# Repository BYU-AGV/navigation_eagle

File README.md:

# navigation_eagle
eagle projects for the navigation team.

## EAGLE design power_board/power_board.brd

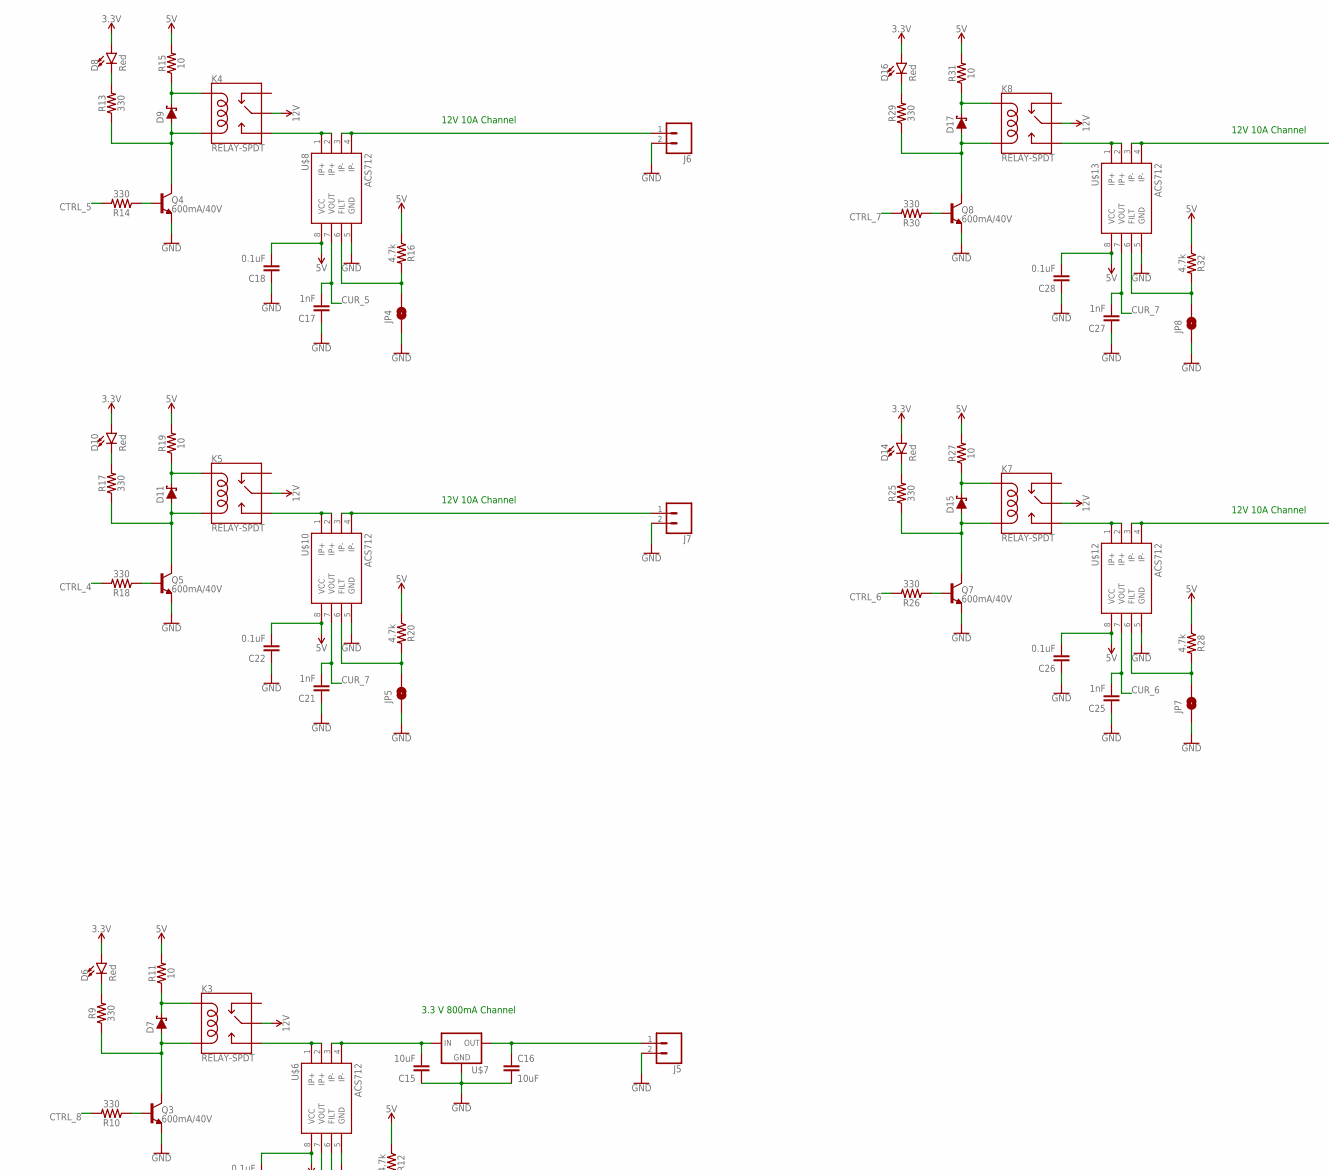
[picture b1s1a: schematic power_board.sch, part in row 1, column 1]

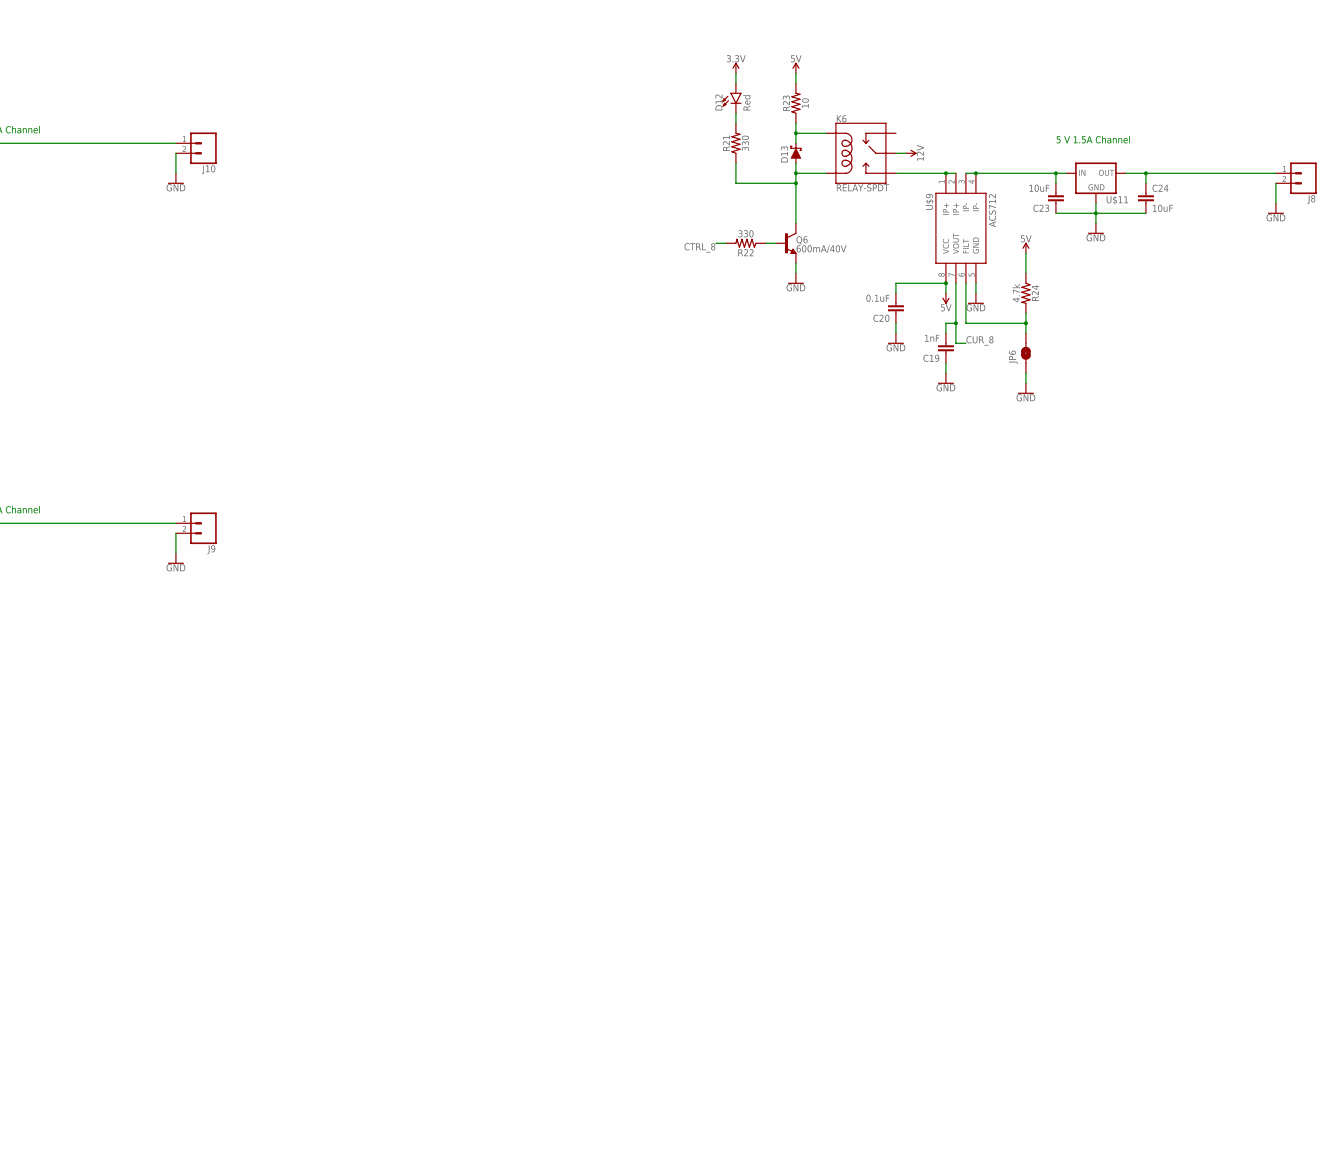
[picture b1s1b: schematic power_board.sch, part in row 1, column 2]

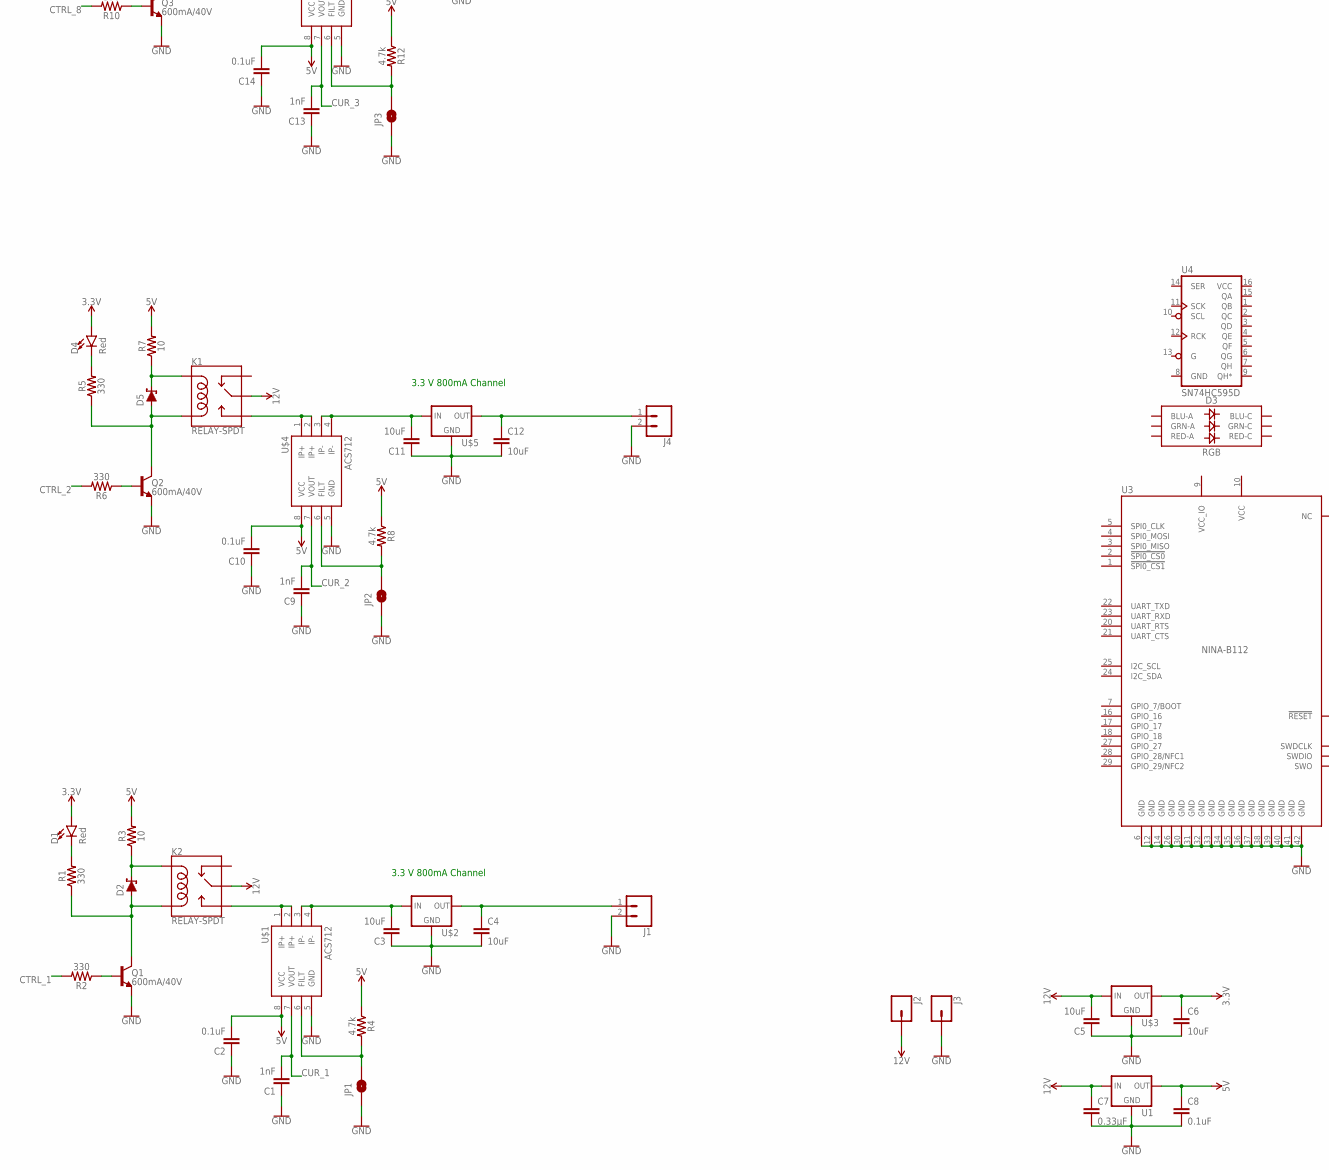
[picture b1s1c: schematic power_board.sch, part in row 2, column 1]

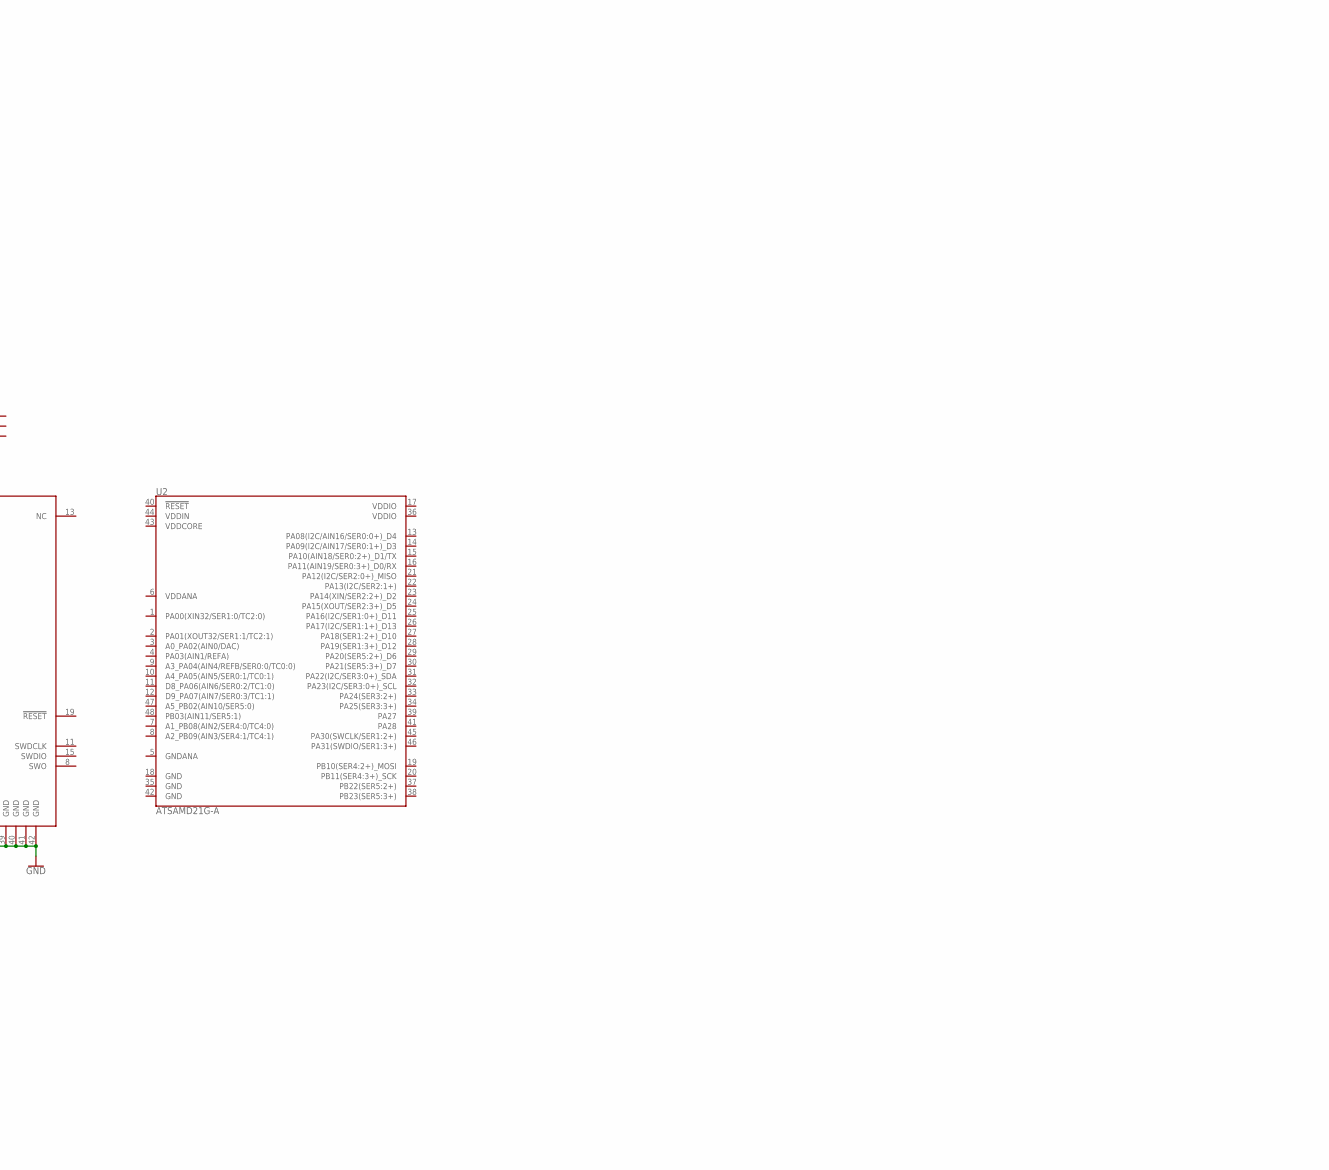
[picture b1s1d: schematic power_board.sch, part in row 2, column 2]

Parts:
C1, C9, C13, C17, C19, C21, C25, C27: 1nF; 0603
C2, C8, C10, C14, C18, C20, C22, C26, C28: 0.1uF; 0603
C3, C4, C5, C6, C11, C12, C15, C16, C23, C24: 10uF; 0603
C7: 0.33µF; 0805
D1, D4, D6, D8, D10, D12, D14, D16: Red; LED-0603
D2, D5, D7, D9, D11, D13, D15, D17: 1A/23V/620mV; SOD-323
D3: RGB; PLCC-6-LED
J1, J4, J5, J6, J7, J8, J9, J10: CONN_023.5MM; SCREWTERMINAL-3.5MM-2
J2, J3: CONN_01PTH_2MM; 1X01_2MM
JP1, JP2, JP3, JP4, JP5, JP6, JP7, JP8: JUMPER-SMT_2_NO_NO-SILK_ROUND; SMT-JUMPER_2_NO_NO-SILK_ROUND
K1, K2, K3, K4, K5, K6, K7, K8: RELAY-SPDT; RELAY_G5LE
Q1, Q2, Q3, Q4, Q5, Q6, Q7, Q8: 600mA/40V; SOT23-3
R1, R2, R5, R6, R9, R10, R13, R14, R17, R18, R21, R22, R25, R26, R29, R30: 330; 0603
R3, R7, R11, R15, R19, R23, R27, R31: 10; 0603
R4, R8, R12, R16, R20, R24, R28, R32: 4.7k; 0603
U1: V_REG_78XX-TO-220; TO-220-ALT
U2: ATSAMD21G-A; TQFP-48
U3: NINA-B112; NINA112-42
U4: SN74HC595D; SO16
U$1, U$4, U$6, U$8, U$9, U$10, U$12, U$13: ACS712; SO08
U$2, U$3, U$5, U$7: 3.3V Voltage Regulator; SOT223
U$11: 3.3V Voltage Regulator; TO-220-ALT

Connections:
3.3V: C6.1, D1.A, D4.A, D6.A, D8.A, D10.A, D12.A, D14.A, D16.A, U$3.2 (OUT)
5V: C2.2, C8.1, C10.2, C14.2, C18.2, C20.2, C22.2, C26.2, C28.2, R3.2, R4.1, R7.2, R8.1, R11.2, R12.1, R15.2, R16.1, R19.2, R20.1, R23.2, R24.1, R27.2, R28.1, R31.2, R32.1, U1.OUT, U$1.8 (VCC), U$4.8 (VCC), U$6.8 (VCC), U$8.8 (VCC), U$9.8 (VCC), U$10.8 (VCC), U$12.8 (VCC), U$13.8 (VCC)
12V: C5.2, C7.1, J2.1, K1.1 (MAIN), K2.1 (MAIN), K3.1 (MAIN), K4.1 (MAIN), K5.1 (MAIN), K6.1 (MAIN), K7.1 (MAIN), K8.1 (MAIN), U1.IN, U$3.3 (IN)
CTRL_1: R2.2
CTRL_2: R6.2
CTRL_4: R18.2
CTRL_5: R14.2
CTRL_6: R26.2
CTRL_7: R30.2
CTRL_8: R10.2, R22.2
CUR_1: C1.2, U$1.7 (VOUT)
CUR_2: C9.2, U$4.7 (VOUT)
CUR_3: C13.2, U$6.7 (VOUT)
CUR_5: C17.2, U$8.7 (VOUT)
CUR_6: C25.2, U$12.7 (VOUT)
CUR_7: C21.2, C27.2, U$10.7 (VOUT), U$13.7 (VOUT)
CUR_8: C19.2, U$9.7 (VOUT)
GND: C1.1, C2.1, C3.1, C4.2, C5.1, C6.2, C7.2, C8.2, C9.1, C10.1, C11.1, C12.2, C13.1, C14.1, C15.1, C16.2, C17.1, C18.1, C19.1, C20.1, C21.1, C22.1, C23.1, C24.2, C25.1, C26.1, C27.1, C28.1, J1.2, J3.1, J4.2, J5.2, J6.2, J7.2, J8.2, J9.2, J10.2, JP1.1, JP2.1, JP3.1, JP4.1, JP5.1, JP6.1, JP7.1, JP8.1, Q1.2 (E), Q2.2 (E), Q3.2 (E), Q4.2 (E), Q5.2 (E), Q6.2 (E), Q7.2 (E), Q8.2 (E), U1.GND, U3.6 (GND), U3.12 (GND), U3.14 (GND), U3.26 (GND), U3.30 (GND), U3.31 (GND), U3.32 (GND), U3.33 (GND), U3.34 (GND), U3.35 (GND), U3.36 (GND), U3.37 (GND), U3.38 (GND), U3.39 (GND), U3.40 (GND), U3.41 (GND), U3.42 (GND), U4.8 (GND), U$1.5 (GND), U$2.1 (GND), U$3.1 (GND), U$4.5 (GND), U$5.1 (GND), U$6.5 (GND), U$7.1 (GND), U$8.5 (GND), U$9.5 (GND), U$10.5 (GND), U$11.GND, U$12.5 (GND), U$13.5 (GND)
unnamed: K2.3 (NO), U$1.1 (IP+), U$1.2 (IP+)
unnamed: C3.2, U$1.3 (IP-), U$1.4 (IP-), U$2.3 (IN)
unnamed: C4.1, J1.1, U$2.2 (OUT)
unnamed: D2.A, K2.5 (COIL2), Q1.3 (C), R1.1
unnamed: D2.C, K2.2 (COIL1), R3.1
unnamed: D1.C, R1.2
unnamed: JP1.2, R4.2, U$1.6 (FILT)
unnamed: D5.A, K1.5 (COIL2), Q2.3 (C), R5.1
unnamed: Q1.1 (B), R2.1
unnamed: D5.C, K1.2 (COIL1), R7.1
unnamed: D4.C, R5.2
unnamed: Q2.1 (B), R6.1
unnamed: C11.2, U$4.3 (IP-), U$4.4 (IP-), U$5.3 (IN)
unnamed: K1.3 (NO), U$4.1 (IP+), U$4.2 (IP+)
unnamed: JP2.2, R8.2, U$4.6 (FILT)
unnamed: C12.1, J4.1, U$5.2 (OUT)
unnamed: D7.A, K3.5 (COIL2), Q3.3 (C), R9.1
unnamed: D7.C, K3.2 (COIL1), R11.1
unnamed: D6.C, R9.2
unnamed: Q3.1 (B), R10.1
unnamed: C15.2, U$6.3 (IP-), U$6.4 (IP-), U$7.3 (IN)
unnamed: K3.3 (NO), U$6.1 (IP+), U$6.2 (IP+)
unnamed: JP3.2, R12.2, U$6.6 (FILT)
unnamed: C16.1, J5.1, U$7.2 (OUT)
unnamed: D9.A, K4.5 (COIL2), Q4.3 (C), R13.1
unnamed: J7.1, U$10.3 (IP-), U$10.4 (IP-)
unnamed: D9.C, K4.2 (COIL1), R15.1
unnamed: D8.C, R13.2
unnamed: Q4.1 (B), R14.1
unnamed: K4.3 (NO), U$8.1 (IP+), U$8.2 (IP+)
unnamed: JP4.2, R16.2, U$8.6 (FILT)
unnamed: J6.1, U$8.3 (IP-), U$8.4 (IP-)
unnamed: D11.A, K5.5 (COIL2), Q5.3 (C), R17.1
unnamed: D11.C, K5.2 (COIL1), R19.1
unnamed: D10.C, R17.2
unnamed: Q5.1 (B), R18.1
unnamed: D13.A, K6.5 (COIL2), Q6.3 (C), R21.1
unnamed: K5.3 (NO), U$10.1 (IP+), U$10.2 (IP+)
unnamed: JP5.2, R20.2, U$10.6 (FILT)
unnamed: D13.C, K6.2 (COIL1), R23.1
unnamed: D12.C, R21.2
unnamed: Q6.1 (B), R22.1
unnamed: C23.2, U$9.3 (IP-), U$9.4 (IP-), U$11.IN
unnamed: K6.3 (NO), U$9.1 (IP+), U$9.2 (IP+)
unnamed: JP6.2, R24.2, U$9.6 (FILT)
unnamed: C24.1, J8.1, U$11.OUT
unnamed: D15.A, K7.5 (COIL2), Q7.3 (C), R25.1
unnamed: D15.C, K7.2 (COIL1), R27.1
unnamed: D14.C, R25.2
unnamed: Q7.1 (B), R26.1
unnamed: K7.3 (NO), U$12.1 (IP+), U$12.2 (IP+)
unnamed: JP7.2, R28.2, U$12.6 (FILT)
unnamed: J9.1, U$12.3 (IP-), U$12.4 (IP-)
unnamed: D17.A, K8.5 (COIL2), Q8.3 (C), R29.1
unnamed: D17.C, K8.2 (COIL1), R31.1
unnamed: D16.C, R29.2
unnamed: Q8.1 (B), R30.1
unnamed: K8.3 (NO), U$13.1 (IP+), U$13.2 (IP+)
unnamed: JP8.2, R32.2, U$13.6 (FILT)
unnamed: J10.1, U$13.3 (IP-), U$13.4 (IP-)
VCC: U3.10 (VCC), U4.16 (VCC)
VCC_IO: U3.9 (VCC_IO)

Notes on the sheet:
3.3 V 800mA Channel
12V 10A Channel
5 V 1.5A Channel

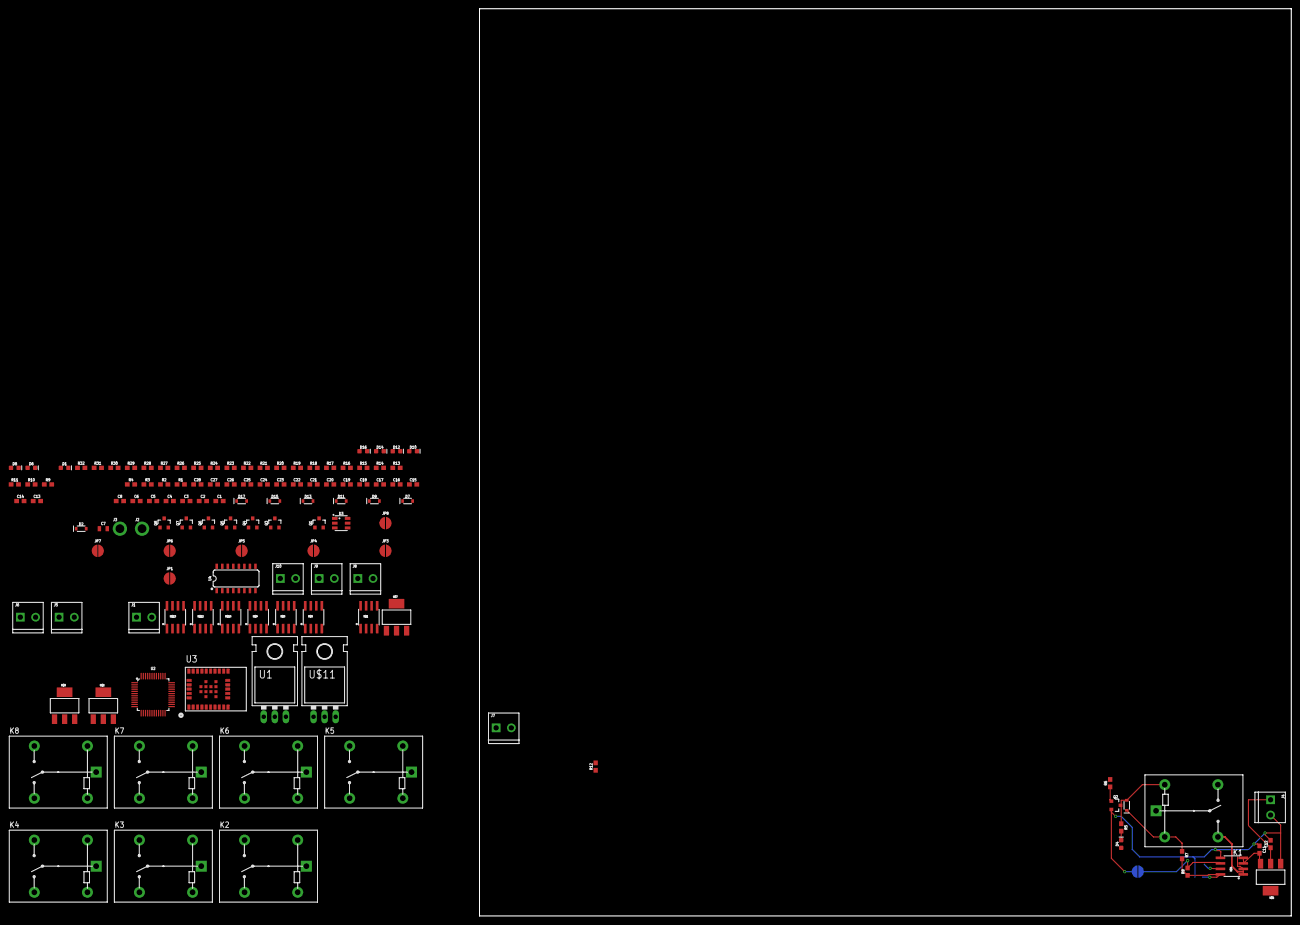
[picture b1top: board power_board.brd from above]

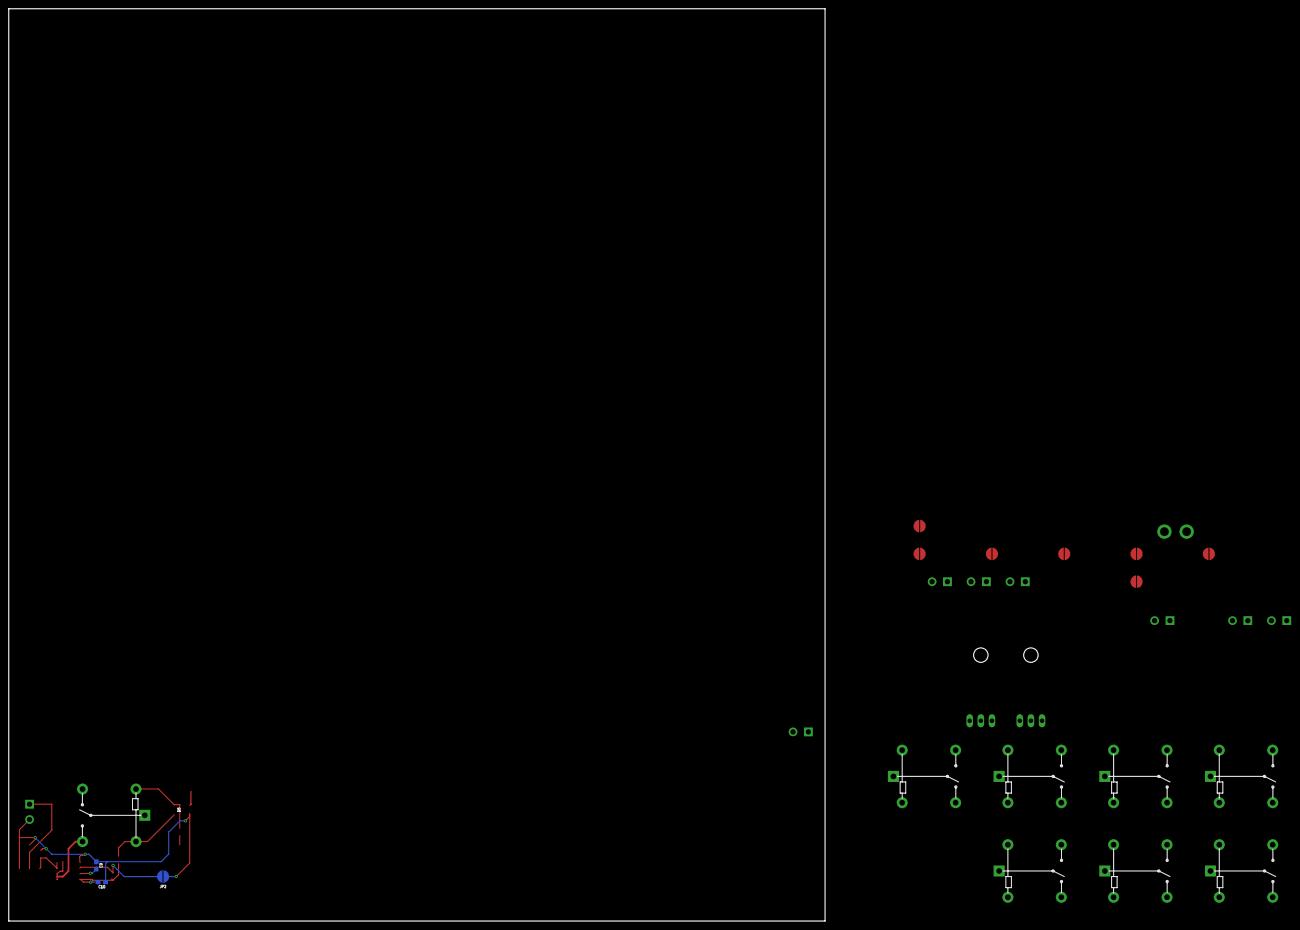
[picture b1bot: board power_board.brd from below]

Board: 2 copper layers, 186.4 x 208.3 mm, 128 parts (3 on the bottom side), 73 nets.

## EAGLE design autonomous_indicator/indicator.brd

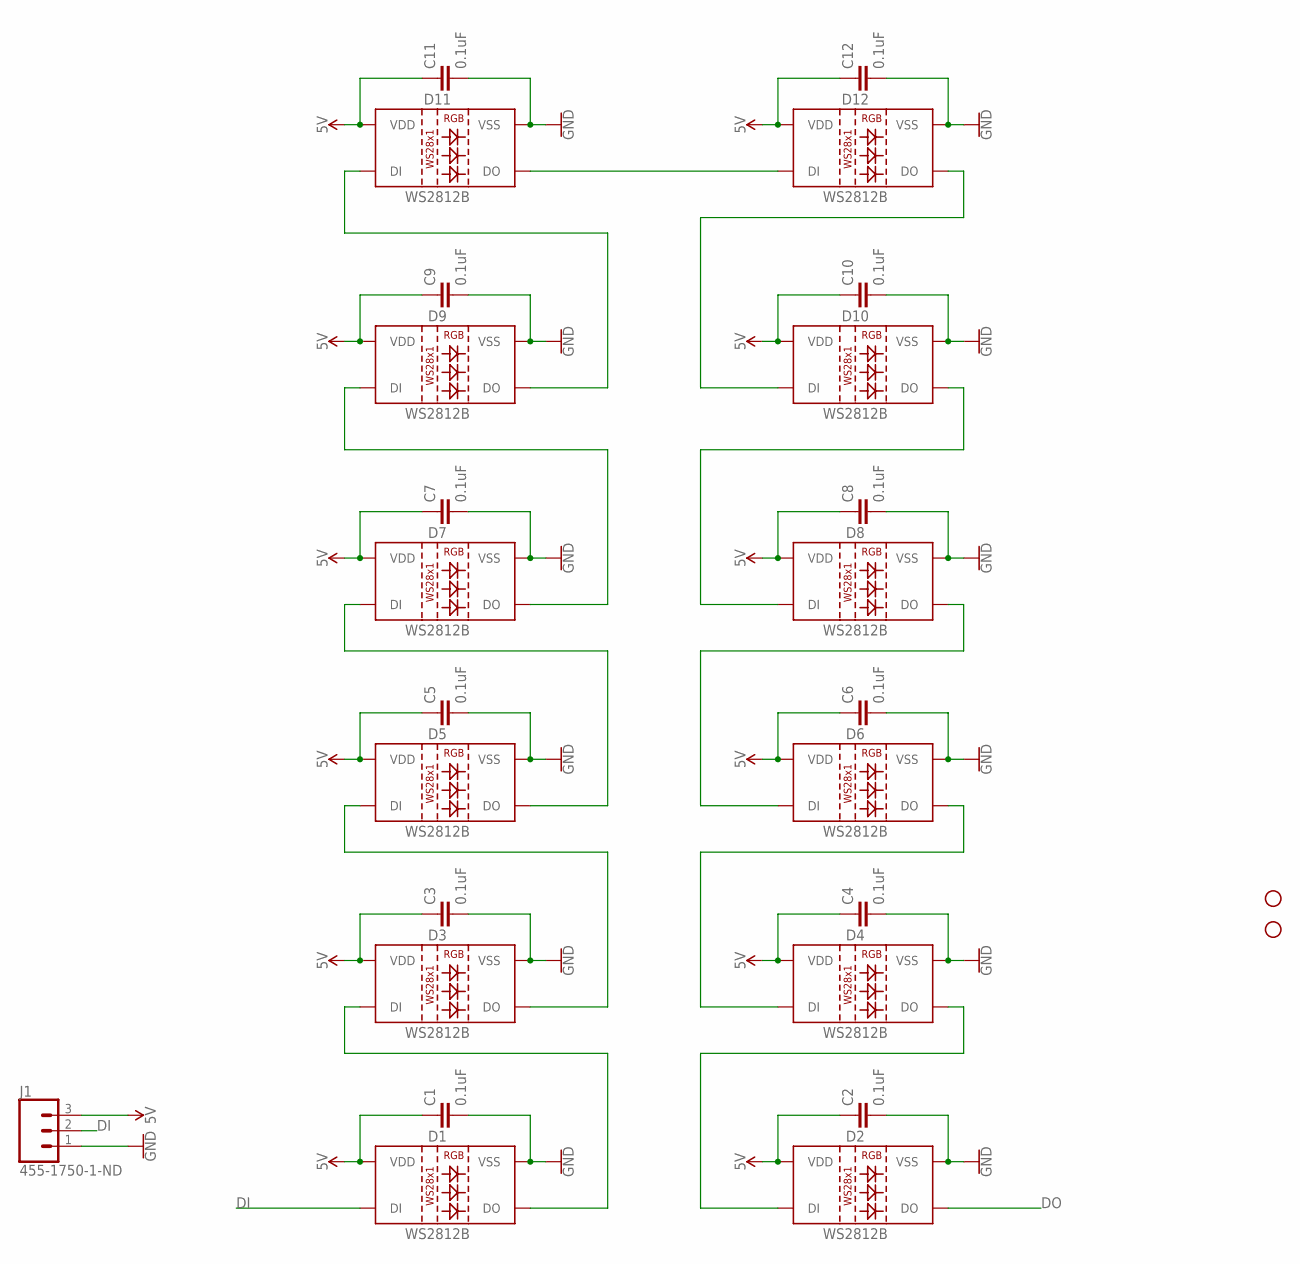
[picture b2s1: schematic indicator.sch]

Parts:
C1, C2, C3, C4, C5, C6, C7, C8, C9, C10, C11, C12: 0.1uF; 0603
D1, D2, D3, D4, D5, D6, D7, D8, D9, D10, D11, D12: WS2812B
H1, H2: STAND-OFF
J1: 455-1750-1-ND; 1X03

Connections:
5V: C1.1, C2.1, C3.1, C4.1, C5.1, C6.1, C7.1, C8.1, C9.1, C10.1, C11.1, C12.1, D1.1 (VDD), D2.1 (VDD), D3.1 (VDD), D4.1 (VDD), D5.1 (VDD), D6.1 (VDD), D7.1 (VDD), D8.1 (VDD), D9.1 (VDD), D10.1 (VDD), D11.1 (VDD), D12.1 (VDD), J1.3
DI: D1.4 (DI), J1.2
DO: D2.2 (DO)
GND: C1.2, C2.2, C3.2, C4.2, C5.2, C6.2, C7.2, C8.2, C9.2, C10.2, C11.2, C12.2, D1.3 (VSS), D2.3 (VSS), D3.3 (VSS), D4.3 (VSS), D5.3 (VSS), D6.3 (VSS), D7.3 (VSS), D8.3 (VSS), D9.3 (VSS), D10.3 (VSS), D11.3 (VSS), D12.3 (VSS), J1.1
unnamed: D1.2 (DO), D3.4 (DI)
unnamed: D3.2 (DO), D5.4 (DI)
unnamed: D5.2 (DO), D7.4 (DI)
unnamed: D7.2 (DO), D9.4 (DI)
unnamed: D9.2 (DO), D11.4 (DI)
unnamed: D11.2 (DO), D12.4 (DI)
unnamed: D10.4 (DI), D12.2 (DO)
unnamed: D8.4 (DI), D10.2 (DO)
unnamed: D6.4 (DI), D8.2 (DO)
unnamed: D4.4 (DI), D6.2 (DO)
unnamed: D2.4 (DI), D4.2 (DO)

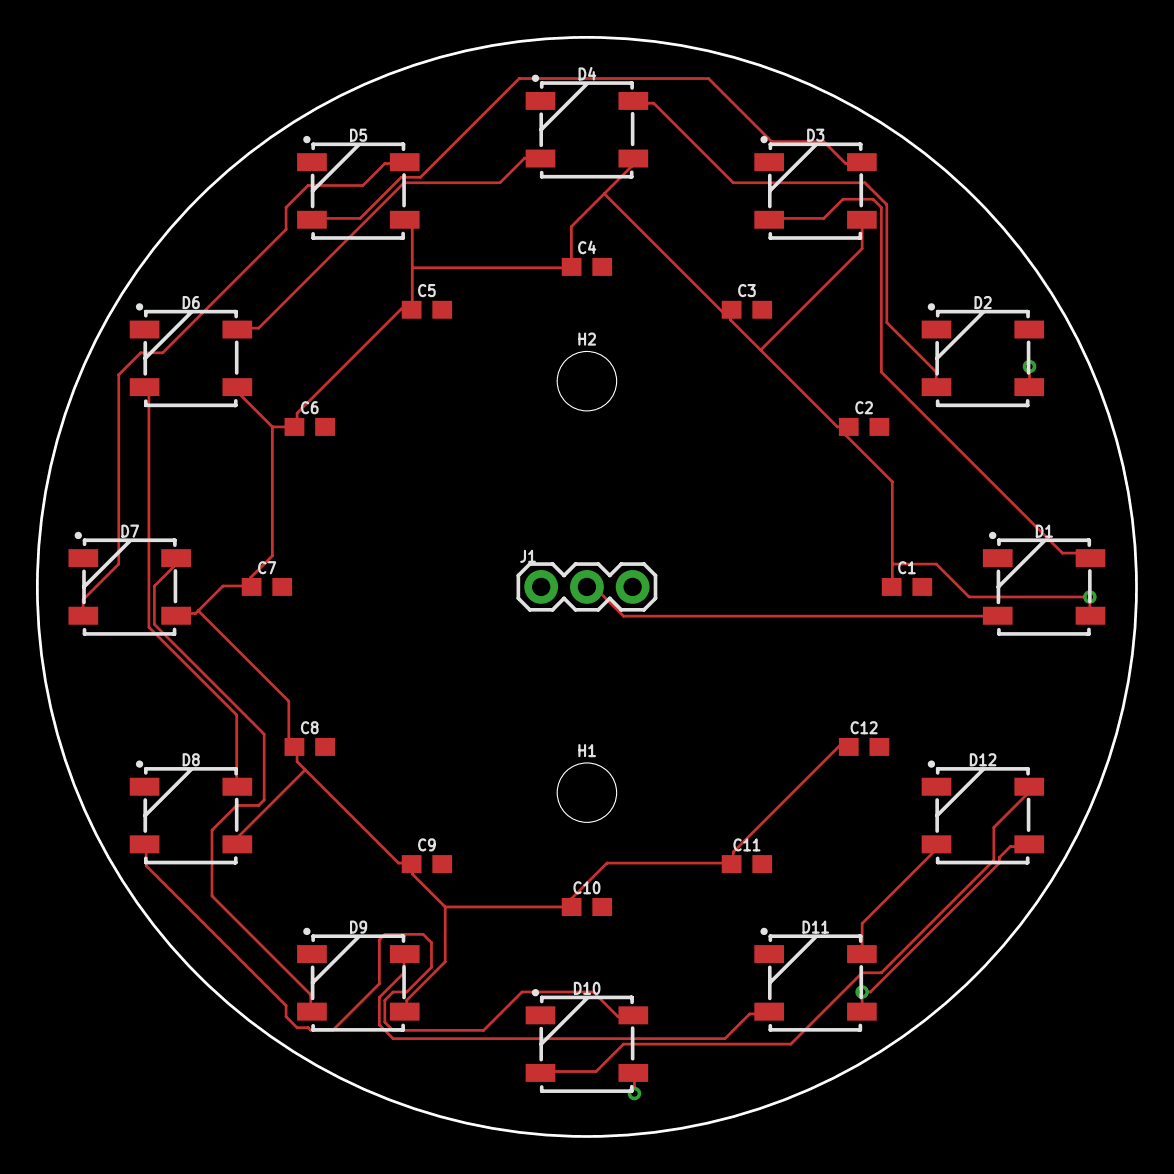
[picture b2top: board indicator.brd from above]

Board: 2 copper layers, 61.1 x 61.1 mm, 27 parts (0 on the bottom side), 14 nets.

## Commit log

2019-10-19 Added an eagle file
2019-10-19 Added some libraries
2019-11-01 Added ATSAMD21 Family datasheet
2019-11-01 Added SAM-M8Q datasheets
2019-11-01 Added ACS712 current sensor datasheet
2019-11-01 Added LED WS2812b datasheet
2019-11-02 Added IMU schematic
2019-11-02 added schematic for gps connectors
2019-11-03 Added gps board and datasheets
2019-11-03 Started working on power board
2019-11-03 Added some datasheets
2019-11-03 Started work on the indicator board
2019-11-04 Started adding NINA-B1
2019-11-27 Updated the schematics and added some more datasheets
2019-12-07 Workedd on powerboard
2019-12-07 Set up one channel
2020-01-07 worked on gps schematic

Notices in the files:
parts and their libraries:
SparkFun-Capacitors: Licensing: Creative Commons ShareAlike 4.0 International - https://creativecommons.org/licenses/by-sa/4.0
